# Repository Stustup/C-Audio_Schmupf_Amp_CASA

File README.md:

# Schmupf-Amp (CASA)
Small Stereo Headphone Amp with microphone passthrough fitting into a nice case.

Simple leader follower parallel opamp topology.

# Signal Path 
Input -> Filter -> Input switch -> Input Buffer -> Volume control -> Voltage Gain Stage -> Current Gain Stage -> Output

Bipolar linear post regulated power supply derived from 12V with a REC10K +-12V Module. Voltage for the opamps is +-9V.d

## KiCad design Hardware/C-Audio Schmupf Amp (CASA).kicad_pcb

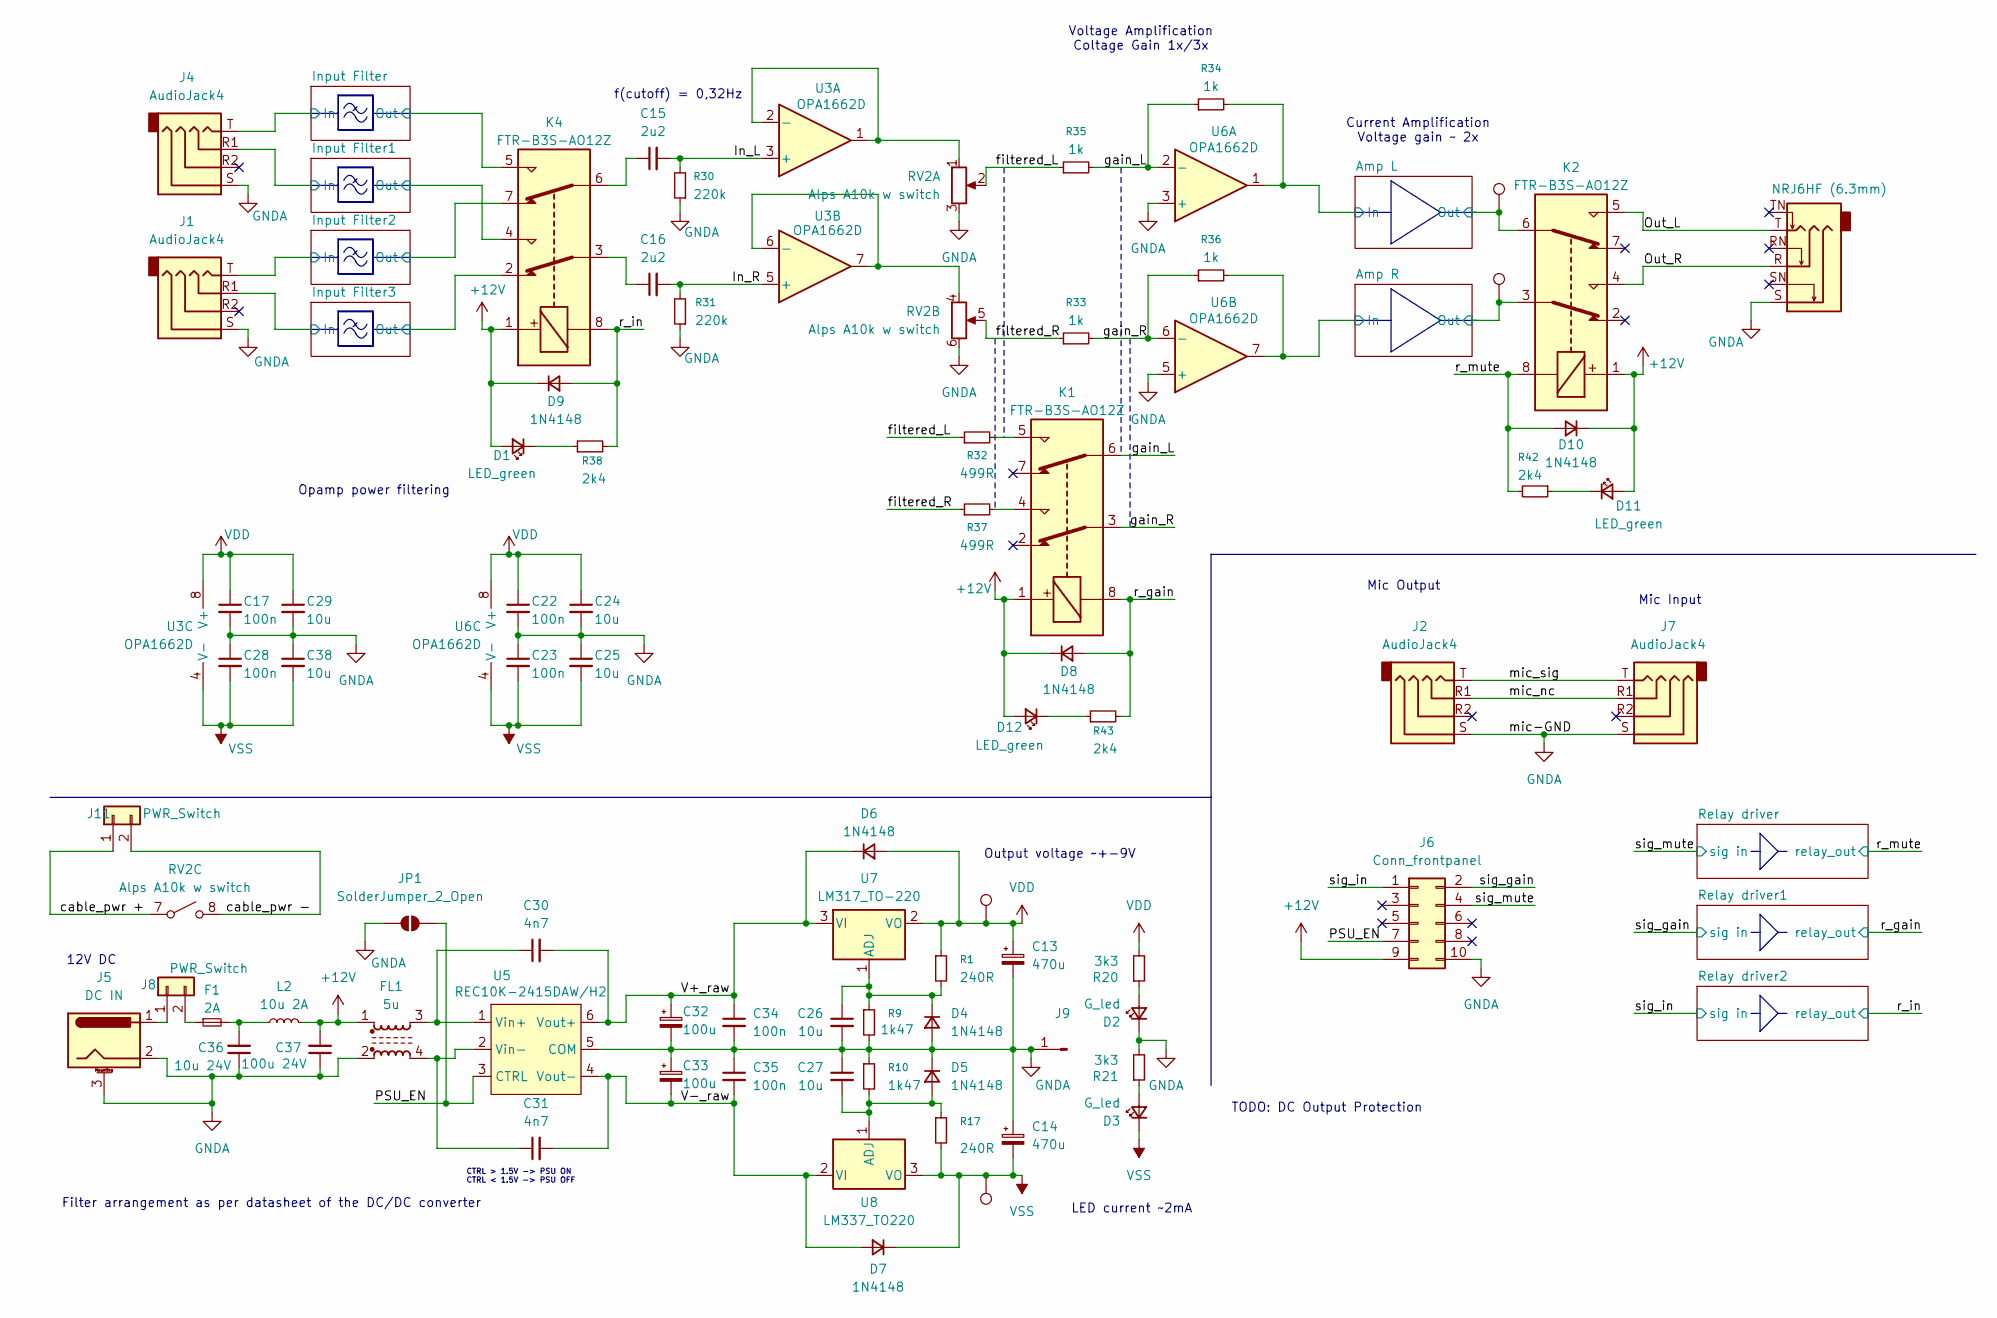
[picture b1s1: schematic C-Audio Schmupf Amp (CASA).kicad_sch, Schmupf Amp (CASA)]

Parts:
C13, C14: 470u; CP_Elec_10x10.5
C15, C16: 2u2; C_Rect_L10.3mm_W5.7mm_P7.50mm_MKS4
C17, C22, C23, C28, C34, C35: 100n; C_0805_2012Metric_Pad1.18x1.45mm_HandSolder
C24, C25, C26, C27, C29, C38: 10u; CP_Elec_4x5.8
C30, C31: 4n7; C_0805_2012Metric_Pad1.18x1.45mm_HandSolder
C32, C33: 100u; CP_Elec_6.3x7.7
C36: 10u 24V; CP_Elec_4x5.8
C37: 100u 24V; CP_Elec_4x5.8
D1, D11, D12: LED_green; LED_0805_2012Metric_Pad1.15x1.40mm_HandSolder
D2, D3: G_led; LED_0805_2012Metric
D4, D5, D6, D7, D8, D9, D10: 1N4148; D_0805_2012Metric_Pad1.15x1.40mm_HandSolder
F1: 2A; Fuseholder_Littelfuse_Nano2_154x
FL1: 5u; L_Bourns_SRF1260
J1, J2, J4, J7: AudioJack4; CLIFF_FC68125
J3: NRJ6HF (6.3mm); Jack_6.35mm_Neutrik_NMJ6HFD2_Horizontal
J5: DC IN; BarrelJack_CUI_PJ-102AH_Horizontal
J6: Conn_frontpanel; IDC-Header_2x05_P2.54mm_Vertical
J8, J11: PWR_Switch; TestPoint_2Pads_Pitch2.54mm_Drill0.8mm
J9: GND Conn; PinHeader_1x01_P1.00mm_Vertical
JP1: SolderJumper_2_Open; SolderJumper-2_P1.3mm_Open_TrianglePad1.0x1.5mm
K1, K2, K4: FTR-B3S-AO12Z; Relay_Fujitsu_FTR-B3S
L2: 10u 2A; L_APV_ANR4010
R1, R17: 240R; R_0805_2012Metric_Pad1.20x1.40mm_HandSolder
R9, R10: 1k47; R_0805_2012Metric_Pad1.20x1.40mm_HandSolder
R20, R21: 3k3; R_0805_2012Metric_Pad1.20x1.40mm_HandSolder
R30, R31: 220k; R_0805_2012Metric_Pad1.20x1.40mm_HandSolder
R32, R37: 499R; R_0805_2012Metric_Pad1.20x1.40mm_HandSolder
R33, R34, R35, R36: 1k; R_0805_2012Metric_Pad1.20x1.40mm_HandSolder
R38, R42, R43: 2k4; R_0805_2012Metric_Pad1.20x1.40mm_HandSolder
RV2: Alps A10k w switch; Potentiometer_Alps_RK097_Dual_Horizontal_Switch
TP1, TP4: TestPoint; TestPoint_Plated_Hole_D2.0mm
TP2: VDD; TestPoint_Pad_D1.0mm
TP3: VSS; TestPoint_Pad_D1.0mm
U3, U6: OPA1662D; SOIC-8_3.9x4.9mm_P1.27mm
U5: REC10K-2415DAW/H2; REC10K-2415DAWH2
U7: LM317_TO-220; TO-220-3_Vertical
U8: LM337_TO220; TO-220-3_Vertical

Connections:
+12V: C37.2, D1.2 (A), D8.1 (K), D9.1 (K), D10.1 (K), D11.2 (A), D12.2 (A), FL1.1, J6.9, K1.1, K2.1, K4.1, L2.2
/Amp L/In: R34.2, U6.1; also elsewhere on the board
/Amp L/Out: K2.6, TP1.1; also elsewhere on the board
/Amp R/In: R36.2, U6.7; also elsewhere on the board
/Amp R/Out: K2.3, TP4.1; also elsewhere on the board
/In_L: C15.2, R30.2, U3.3 (+)
/In_R: C16.2, R31.2, U3.5 (+)
/Input Filter1/In: J4.R1; also elsewhere on the board
/Input Filter1/Out: K4.4; also elsewhere on the board
/Input Filter2/In: J1.T; also elsewhere on the board
/Input Filter2/Out: K4.7; also elsewhere on the board
/Input Filter3/In: J1.R1; also elsewhere on the board
/Input Filter3/Out: K4.2; also elsewhere on the board
/Input Filter/In: J4.T; also elsewhere on the board
/Input Filter/Out: K4.5; also elsewhere on the board
/Out_L: J3.T, K2.5
/Out_R: J3.R, K2.4
/PSU_EN: J6.7, JP1.1 (A), U5.3 (CTRL)
/V+_raw: C30.2, C32.1, C34.1, D6.1 (K), U5.6 (Vout+), U7.3 (VI)
/V-_raw: C31.2, C33.2, C35.2, D7.2 (A), U5.4 (Vout-), U8.2 (VI)
/cable_pwr +: J11.1, RV2.7
/cable_pwr -: J11.2, RV2.8
/filtered_L: R32.1, R35.1, RV2.2
/filtered_R: R33.1, R37.1, RV2.5
/gain_L: K1.6, R34.1, R35.2, U6.2 (-)
/gain_R: K1.3, R33.2, R36.1, U6.6 (-)
/mic_nc: J2.R1, J7.R1
/mic_sig: J2.T, J7.T
/r_gain: D8.2 (A), K1.8, R43.2; also elsewhere on the board
/r_in: D9.2 (A), K4.8, R38.2; also elsewhere on the board
/r_mute: D10.2 (A), K2.8, R42.2; also elsewhere on the board
/sig_gain: J6.2; also elsewhere on the board
/sig_in: J6.1; also elsewhere on the board
/sig_mute: J6.4; also elsewhere on the board
GNDA: C13.2, C14.1, C17.2, C22.2, C23.1, C24.2, C25.1, C26.2, C27.1, C28.1, C29.2, C32.2, C33.1, C34.2, C35.1, C36.1, C37.1, C38.1, D2.1 (K), D4.2 (A), D5.1 (K), FL1.2, J1.S, J2.S, J3.S, J4.S, J5.2, J5.3 (MountPin), J6.10, J7.S, J9.1, JP1.2 (B), R9.2, R10.1, R21.2, R30.1, R31.1, RV2.3, RV2.6, U5.5 (COM), U6.3 (+), U6.5 (+); also elsewhere on the board
unnamed: C15.1, K4.6
unnamed: C16.1, K4.3
unnamed: C36.2, F1.2, L2.1
unnamed: D1.1 (K), R38.1
unnamed: D2.2 (A), R20.1
unnamed: D3.2 (A), R21.1
unnamed: C26.1, D4.1 (K), R1.2, R9.1, U7.1 (ADJ)
unnamed: C27.2, D5.2 (A), R10.2, R17.1, U8.1 (ADJ)
unnamed: D11.1 (K), R42.1
unnamed: D12.1 (K), R43.1
unnamed: J5.1, J8.1
unnamed: F1.1, J8.2
unnamed: K1.4, R37.2
unnamed: K1.5, R32.2
unnamed: RV2.1, U3.1, U3.2 (-)
unnamed: RV2.4, U3.6 (-), U3.7
unnamed: C30.1, FL1.3, U5.1 (Vin+)
unnamed: C31.1, FL1.4, U5.2 (Vin-)
VDD: C13.1, C17.1, C22.1, C24.1, C29.1, D6.2 (A), R1.1, R20.2, TP2.1, U3.8 (V+), U6.8 (V+), U7.2 (VO); also elsewhere on the board
VSS: C14.2, C23.2, C25.2, C28.2, C38.2, D3.1 (K), D7.1 (K), R17.2, TP3.1, U3.4 (V-), U6.4 (V-), U8.3 (VO); also elsewhere on the board

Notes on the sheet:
Output voltage ~+-9V
f(cutoff) = 0,32Hz
Mic Input
Mic Output
Filter arrangement as per datasheet of the DC/DC converter
12V DC
Voltage Amplification Coltage Gain 1x/3x
CTRL > 1.5V -> PSU ON CTRL < 1.5V -> PSU OFF
LED current ~2mA
TODO: DC Output Protection
Current Amplification Voltage gain ~ 2x
Opamp power filtering

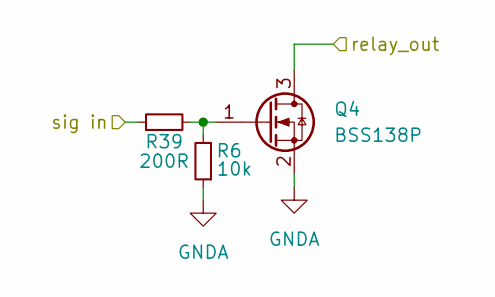
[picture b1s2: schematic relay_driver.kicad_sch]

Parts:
Q4: BSS138P; SOT-23
R6: 10k; R_0805_2012Metric_Pad1.20x1.40mm_HandSolder
R39: 200R; R_0805_2012Metric_Pad1.20x1.40mm_HandSolder

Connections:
/r_mute: Q4.3 (D); also elsewhere on the board
/sig_mute: R39.1; also elsewhere on the board
GNDA: Q4.2 (S), R6.1; also elsewhere on the board
unnamed: Q4.1 (G), R6.2, R39.2

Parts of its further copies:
Q5, Q6: BSS138P; SOT-23
R18, R19: 10k; R_0805_2012Metric_Pad1.20x1.40mm_HandSolder
R40, R41: 200R; R_0805_2012Metric_Pad1.20x1.40mm_HandSolder

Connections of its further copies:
/r_gain: Q5.3 (D); also elsewhere on the board
/r_in: Q6.3 (D); also elsewhere on the board
/sig_gain: R40.1; also elsewhere on the board
/sig_in: R41.1; also elsewhere on the board
GNDA: Q5.2 (S), Q6.2 (S), R18.1, R19.1; also elsewhere on the board
unnamed: Q5.1 (G), R18.2, R40.2
unnamed: Q6.1 (G), R19.2, R41.2

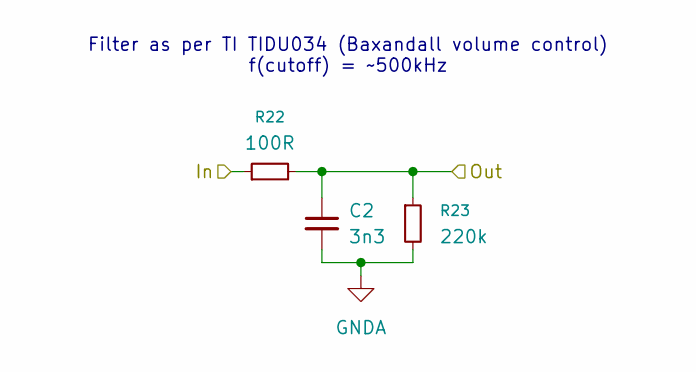
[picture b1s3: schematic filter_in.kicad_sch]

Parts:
C2: 3n3; C_0805_2012Metric_Pad1.18x1.45mm_HandSolder
R22: 100R; R_0805_2012Metric_Pad1.20x1.40mm_HandSolder
R23: 220k; R_0805_2012Metric_Pad1.20x1.40mm_HandSolder

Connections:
/Input Filter/In: R22.1; also elsewhere on the board
/Input Filter/Out: C2.1, R22.2, R23.1; also elsewhere on the board
GNDA: C2.2, R23.2; also elsewhere on the board

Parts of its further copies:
C3, C8, C9: 3n3; C_0805_2012Metric_Pad1.18x1.45mm_HandSolder
R24, R26, R28: 100R; R_0805_2012Metric_Pad1.20x1.40mm_HandSolder
R25, R27, R29: 220k; R_0805_2012Metric_Pad1.20x1.40mm_HandSolder

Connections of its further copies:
/Input Filter1/In: R24.1; also elsewhere on the board
/Input Filter1/Out: C3.1, R24.2, R25.1; also elsewhere on the board
/Input Filter2/In: R26.1; also elsewhere on the board
/Input Filter2/Out: C8.1, R26.2, R27.1; also elsewhere on the board
/Input Filter3/In: R28.1; also elsewhere on the board
/Input Filter3/Out: C9.1, R28.2, R29.1; also elsewhere on the board
GNDA: C3.2, C8.2, C9.2, R25.2, R27.2, R29.2; also elsewhere on the board

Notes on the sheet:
Filter as per TI TIDU034 (Baxandall volume control) f(cutoff) = ~500kHz

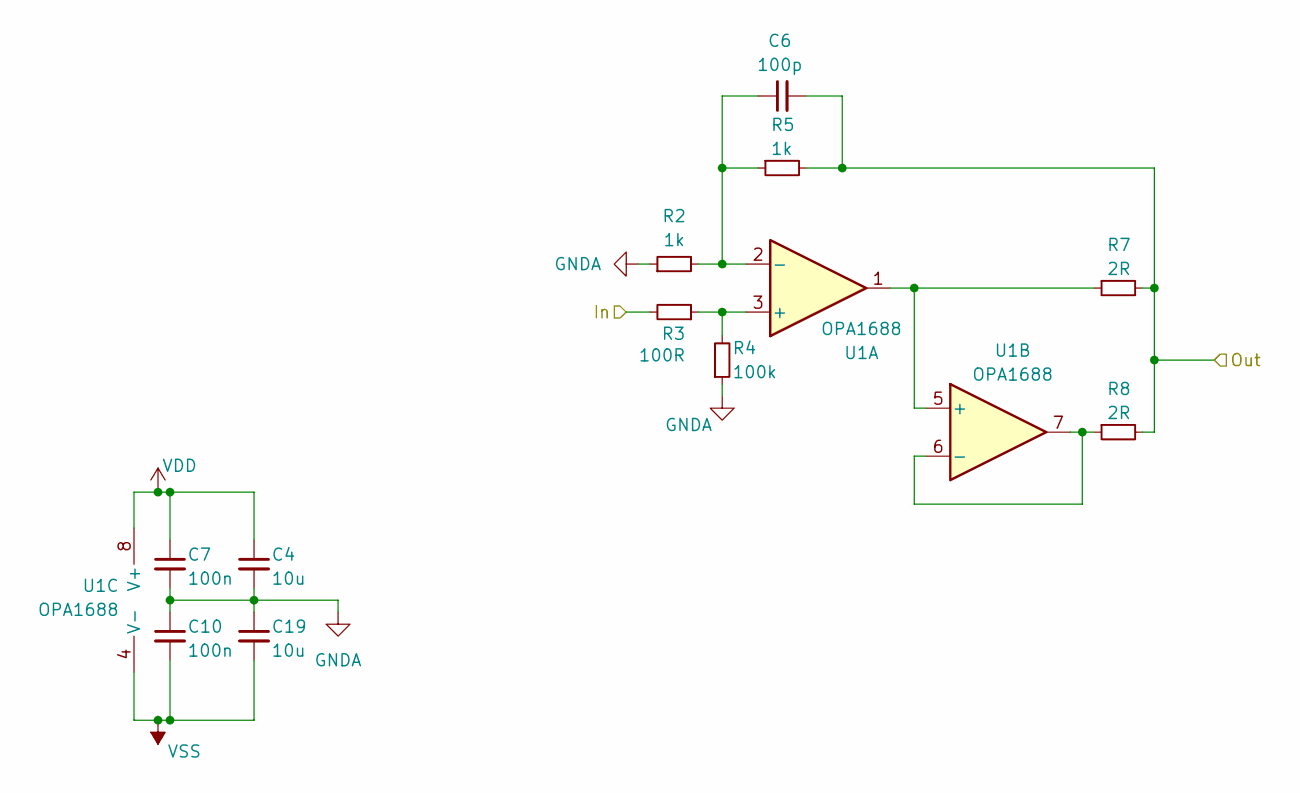
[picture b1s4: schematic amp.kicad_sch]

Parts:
C4, C19: 10u; CP_Elec_4x5.8
C6: 100p; C_0805_2012Metric_Pad1.18x1.45mm_HandSolder
C7, C10: 100n; C_0805_2012Metric_Pad1.18x1.45mm_HandSolder
R2, R5: 1k; R_0805_2012Metric_Pad1.20x1.40mm_HandSolder
R3: 100R; R_0805_2012Metric_Pad1.20x1.40mm_HandSolder
R4: 100k; R_0805_2012Metric_Pad1.20x1.40mm_HandSolder
R7, R8: 2R; R_0805_2012Metric_Pad1.20x1.40mm_HandSolder
U1: OPA1688; SO-8_3.9x4.9mm_P1.27mm

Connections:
/Amp L/In: R3.2; also elsewhere on the board
/Amp L/Out: C6.2, R5.2, R7.2, R8.2; also elsewhere on the board
GNDA: C4.2, C7.2, C10.1, C19.1, R2.1, R4.1; also elsewhere on the board
unnamed: R3.1, R4.2, U1.3 (+)
unnamed: C6.1, R2.2, R5.1, U1.2 (-)
unnamed: R7.1, U1.1, U1.5 (+)
unnamed: R8.1, U1.6 (-), U1.7
VDD: C4.1, C7.1, U1.8 (V+); also elsewhere on the board
VSS: C10.2, C19.2, U1.4 (V-); also elsewhere on the board

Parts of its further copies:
C5, C20: 10u; CP_Elec_4x5.8
C11, C18: 100n; C_0805_2012Metric_Pad1.18x1.45mm_HandSolder
C21: 100p; C_0805_2012Metric_Pad1.18x1.45mm_HandSolder
R11, R14: 1k; R_0805_2012Metric_Pad1.20x1.40mm_HandSolder
R12: 100R; R_0805_2012Metric_Pad1.20x1.40mm_HandSolder
R13: 100k; R_0805_2012Metric_Pad1.20x1.40mm_HandSolder
R15, R16: 2R; R_0805_2012Metric_Pad1.20x1.40mm_HandSolder
U2: OPA1688; SO-8_3.9x4.9mm_P1.27mm

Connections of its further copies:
/Amp R/In: R12.2; also elsewhere on the board
/Amp R/Out: C21.2, R14.2, R15.2, R16.2; also elsewhere on the board
GNDA: C5.2, C11.2, C18.1, C20.1, R11.1, R13.1; also elsewhere on the board
unnamed: R12.1, R13.2, U2.3 (+)
unnamed: C21.1, R11.2, R14.1, U2.2 (-)
unnamed: R15.1, U2.1, U2.5 (+)
unnamed: R16.1, U2.6 (-), U2.7
VDD: C5.1, C11.1, U2.8 (V+); also elsewhere on the board
VSS: C18.2, C20.2, U2.4 (V-); also elsewhere on the board

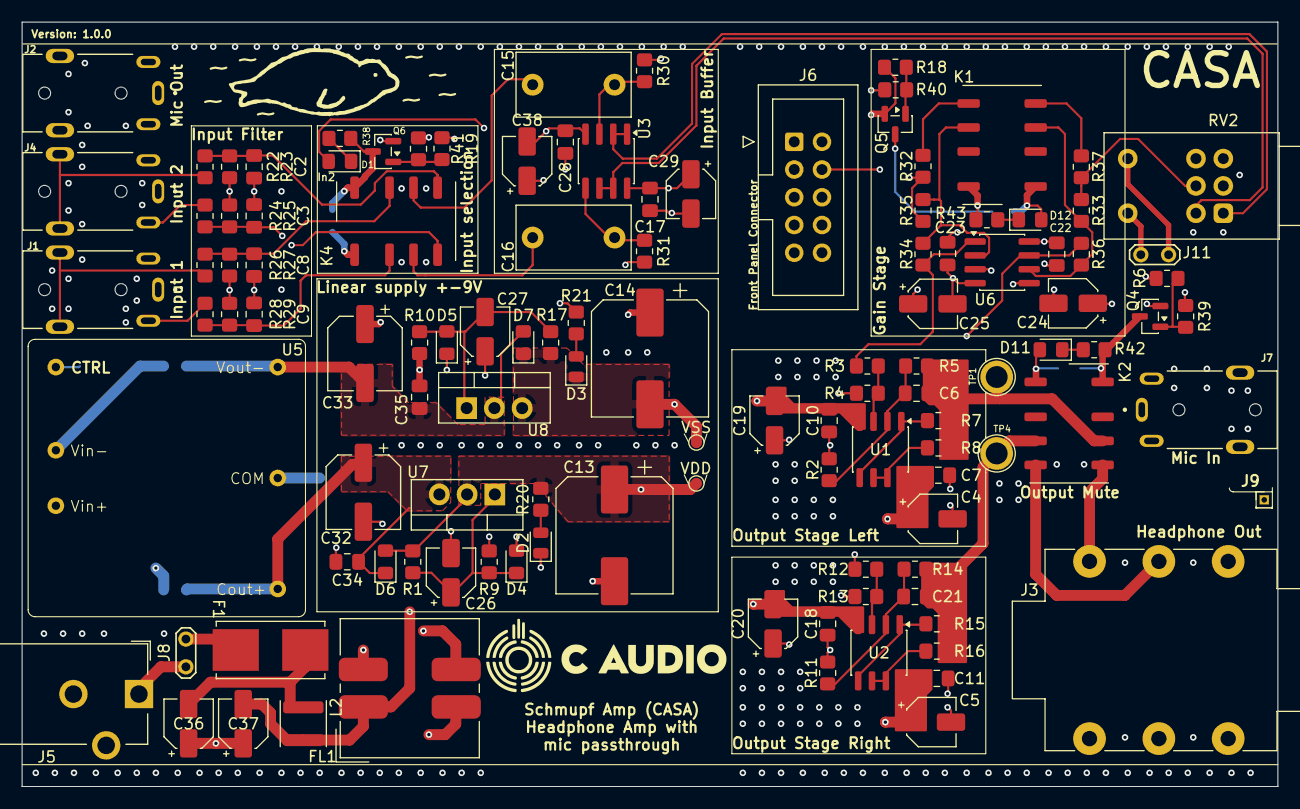
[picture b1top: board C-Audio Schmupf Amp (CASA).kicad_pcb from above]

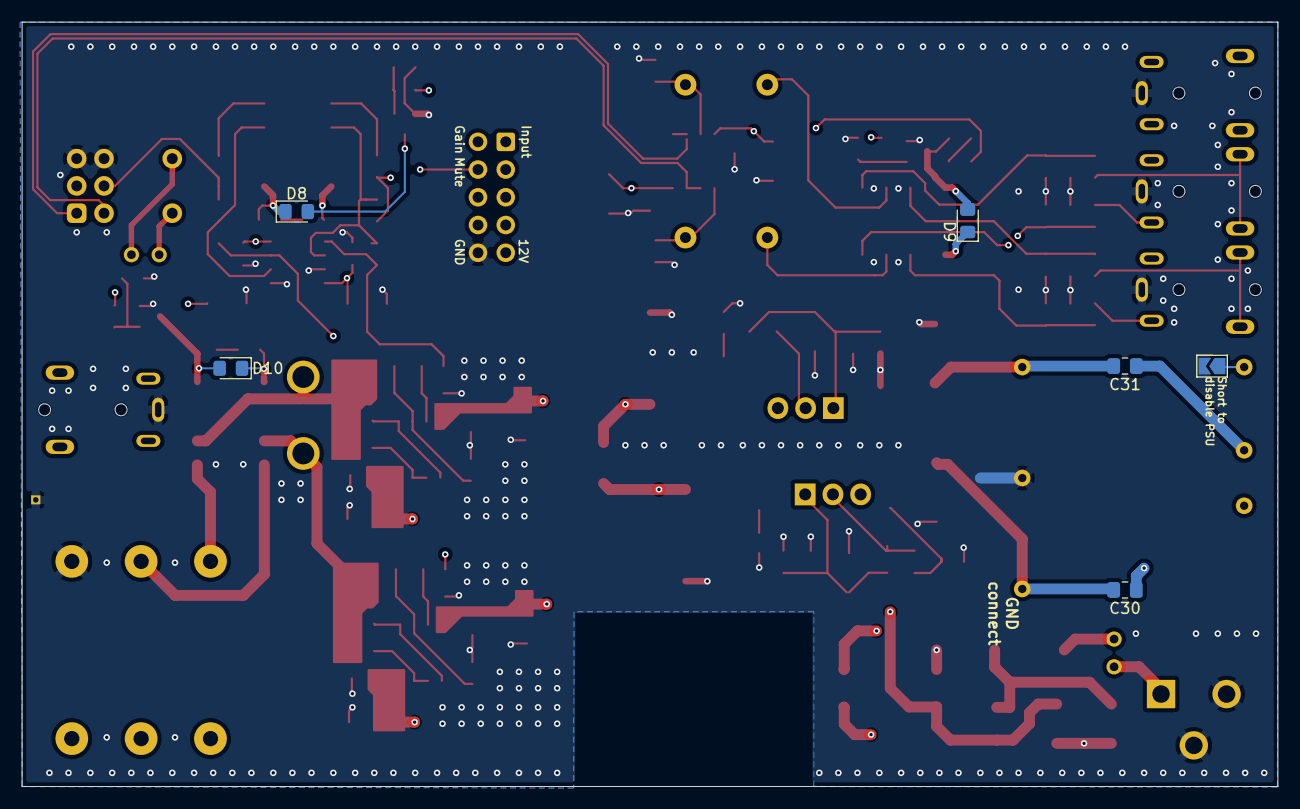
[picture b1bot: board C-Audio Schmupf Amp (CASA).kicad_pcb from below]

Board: 4 copper layers, 115.0 x 70.0 mm, 123 parts (6 on the bottom side), 66 nets.

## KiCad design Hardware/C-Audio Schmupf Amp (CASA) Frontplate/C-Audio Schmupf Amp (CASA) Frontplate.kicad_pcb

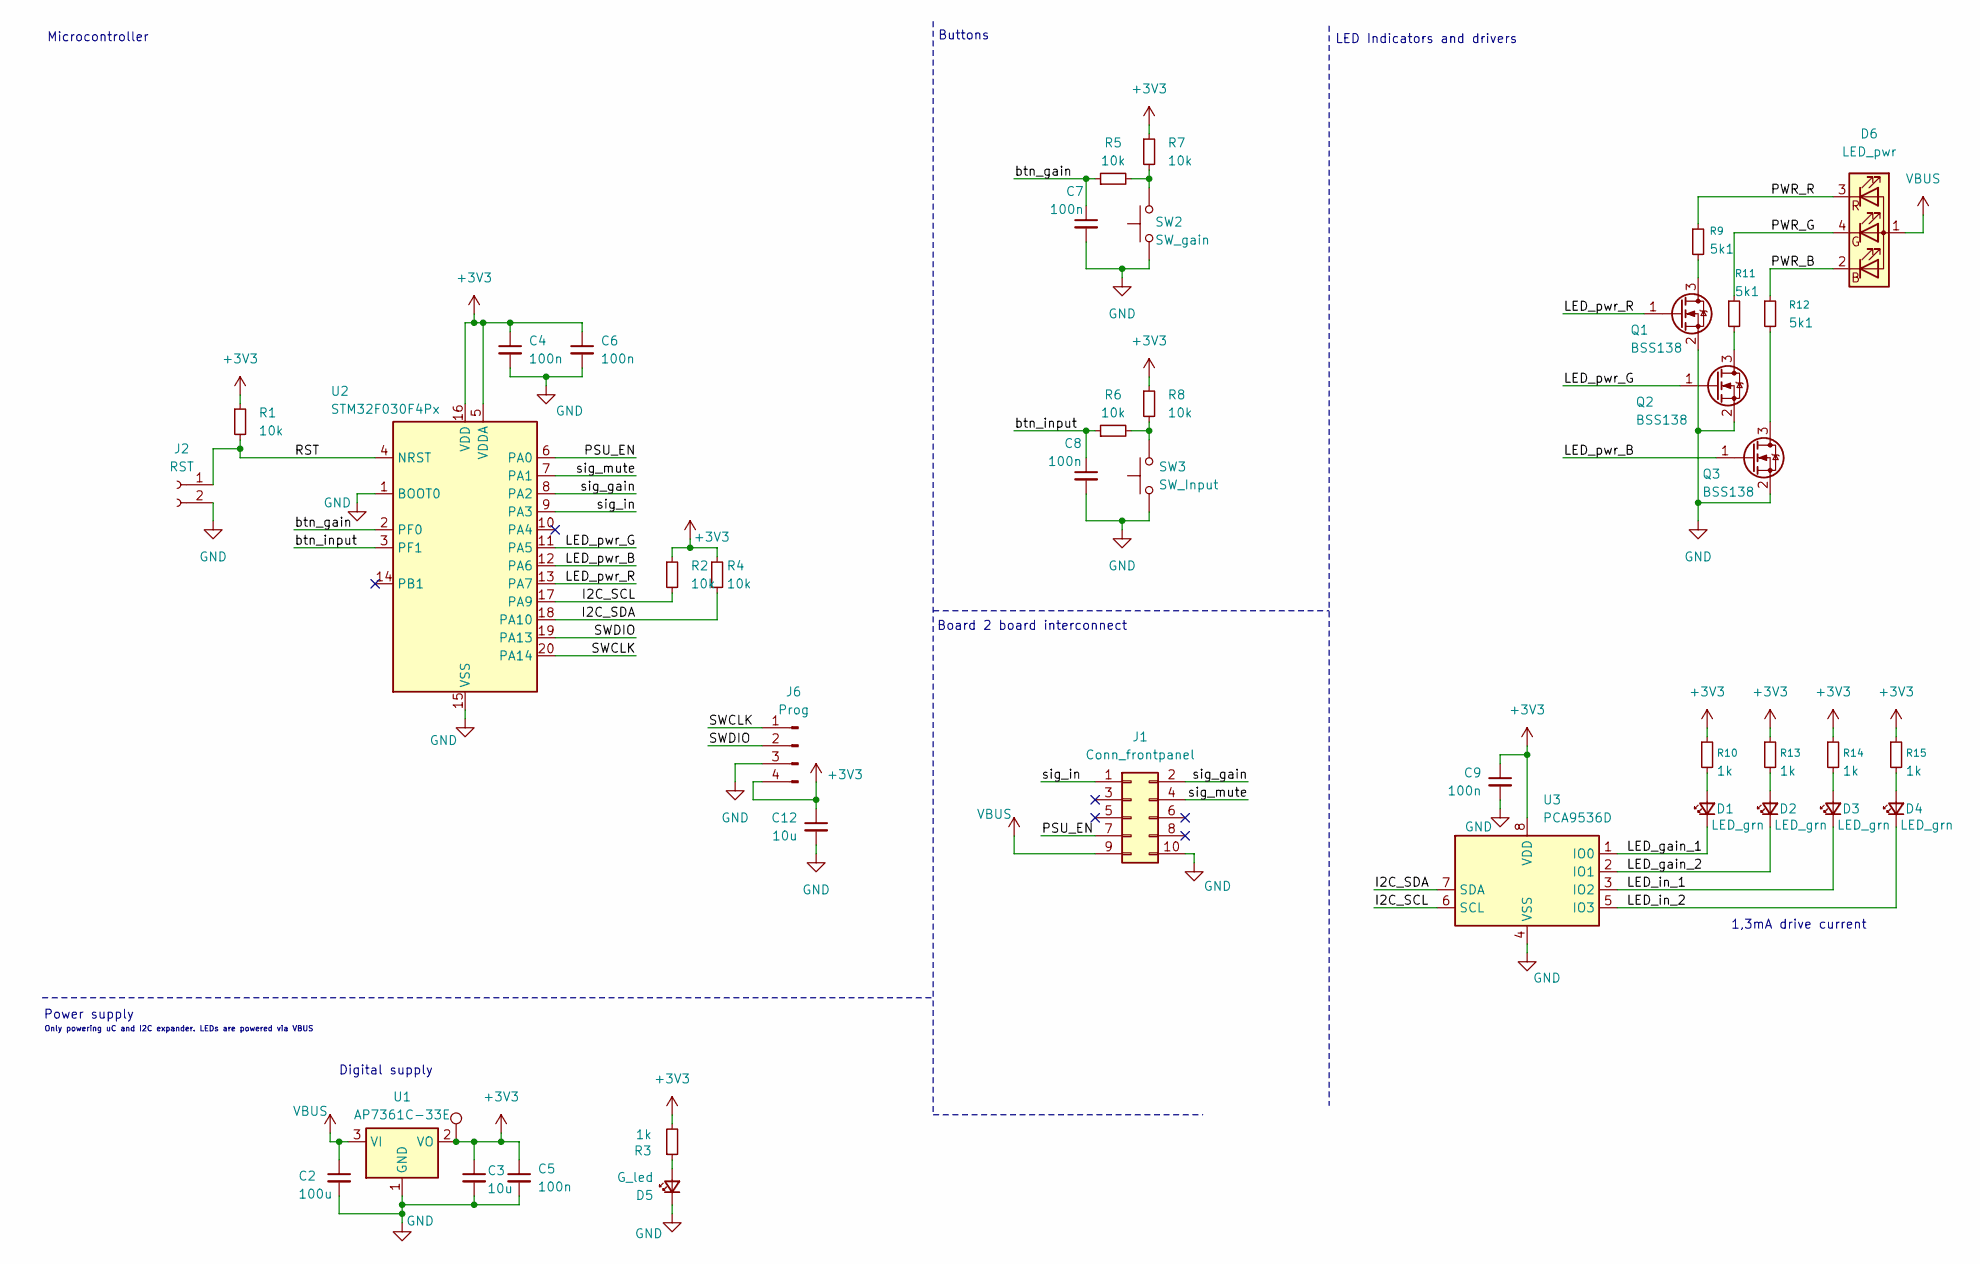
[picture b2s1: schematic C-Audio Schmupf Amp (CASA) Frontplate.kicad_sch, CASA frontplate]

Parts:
C2: 100u; CP_Elec_4x5.8
C3: 10u; C_0805_2012Metric_Pad1.18x1.45mm_HandSolder
C4, C5, C6, C7, C8, C9: 100n; C_0805_2012Metric_Pad1.18x1.45mm_HandSolder
C12: 10u; C_0805_2012Metric_Pad1.18x1.45mm_HandSolder; Mouser Nr. 187-CL21B106KPQNNNE
D1, D2, D3, D4: LED_grn; LED_0805_2012Metric_Pad1.15x1.40mm_HandSolder
D5: G_led; LED_0805_2012Metric_Pad1.15x1.40mm_HandSolder
D6: LED_pwr; LED_RGB_Wuerth-PLCC4_3.2x2.8mm_150141M173100
J1: Conn_frontpanel; IDC-Header_2x05_P2.54mm_Vertical
J2: RST; SolderJumper-2_P1.3mm_Open_TrianglePad1.0x1.5mm
J6: Prog; PinHeader_1x04_P2.54mm_Vertical
Q1, Q2, Q3: BSS138; SOT-23
R1, R2, R4, R5, R6, R7, R8: 10k; R_0805_2012Metric_Pad1.20x1.40mm_HandSolder
R3, R10, R13, R14, R15: 1k; R_0805_2012Metric_Pad1.20x1.40mm_HandSolder
R9, R11, R12: 5k1; R_0805_2012Metric_Pad1.20x1.40mm_HandSolder
SW2: SW_gain; SW_PUSH_6mm_H13mm
SW3: SW_Input; SW_PUSH_6mm_H13mm
TP1: TestPoint; TestPoint_Pad_D1.0mm
U1: AP7361C-33E; SOT-223-3_TabPin2; Mouser Nr. 621-AP7361C-33ER-13
U2: STM32F030F4Px; TSSOP-20_4.4x6.5mm_P0.65mm
U3: PCA9536D; SOIC-8_3.9x4.9mm_P1.27mm

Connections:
/I2C_SCL: R2.2, U2.17 (PA9), U3.6 (SCL)
/I2C_SDA: R4.2, U2.18 (PA10), U3.7 (SDA)
/LED_gain_1: D1.1 (K), U3.1 (IO0)
/LED_gain_2: D2.1 (K), U3.2 (IO1)
/LED_in_1: D3.1 (K), U3.3 (IO2)
/LED_in_2: D4.1 (K), U3.5 (IO3)
/LED_pwr_B: Q3.1 (G), U2.12 (PA6)
/LED_pwr_G: Q2.1 (G), U2.11 (PA5)
/LED_pwr_R: Q1.1 (G), U2.13 (PA7)
/PSU_EN: J1.7, U2.6 (PA0)
/PWR_B: D6.2 (BK), R12.1
/PWR_G: D6.4 (GK), R11.1
/PWR_R: D6.3 (RK), R9.1
/RST: J2.1, R1.2, U2.4 (NRST)
/SWCLK: J6.1, U2.20 (PA14)
/SWDIO: J6.2, U2.19 (PA13)
/btn_gain: C7.1, R5.1, U2.2 (PF0)
/btn_input: C8.1, R6.1, U2.3 (PF1)
/sig_gain: J1.2, U2.8 (PA2)
/sig_in: J1.1, U2.9 (PA3)
/sig_mute: J1.4, U2.7 (PA1)
GND: C2.2, C3.2, C4.2, C5.2, C6.2, C7.2, C8.2, C9.2, C12.2, D5.1 (K), J1.10, J2.2, J6.3, Q1.2 (S), Q2.2 (S), Q3.2 (S), SW2.1, SW3.1, U1.1 (GND), U2.1 (BOOT0), U2.15 (VSS), U3.4 (VSS)
unnamed: D1.2 (A), R10.2
unnamed: D2.2 (A), R13.2
unnamed: D3.2 (A), R14.2
unnamed: D4.2 (A), R15.2
unnamed: D5.2 (A), R3.1
unnamed: Q1.3 (D), R9.2
unnamed: Q2.3 (D), R11.2
unnamed: Q3.3 (D), R12.2
unnamed: R5.2, R7.2, SW2.2
unnamed: R6.2, R8.2, SW3.2

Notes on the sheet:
Board 2 board interconnect
Microcontroller
Digital supply
Buttons
1,3mA drive current
Only powering uC and I2C expander. LEDs are powered via VBUS
Power supply
LED Indicators and drivers

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
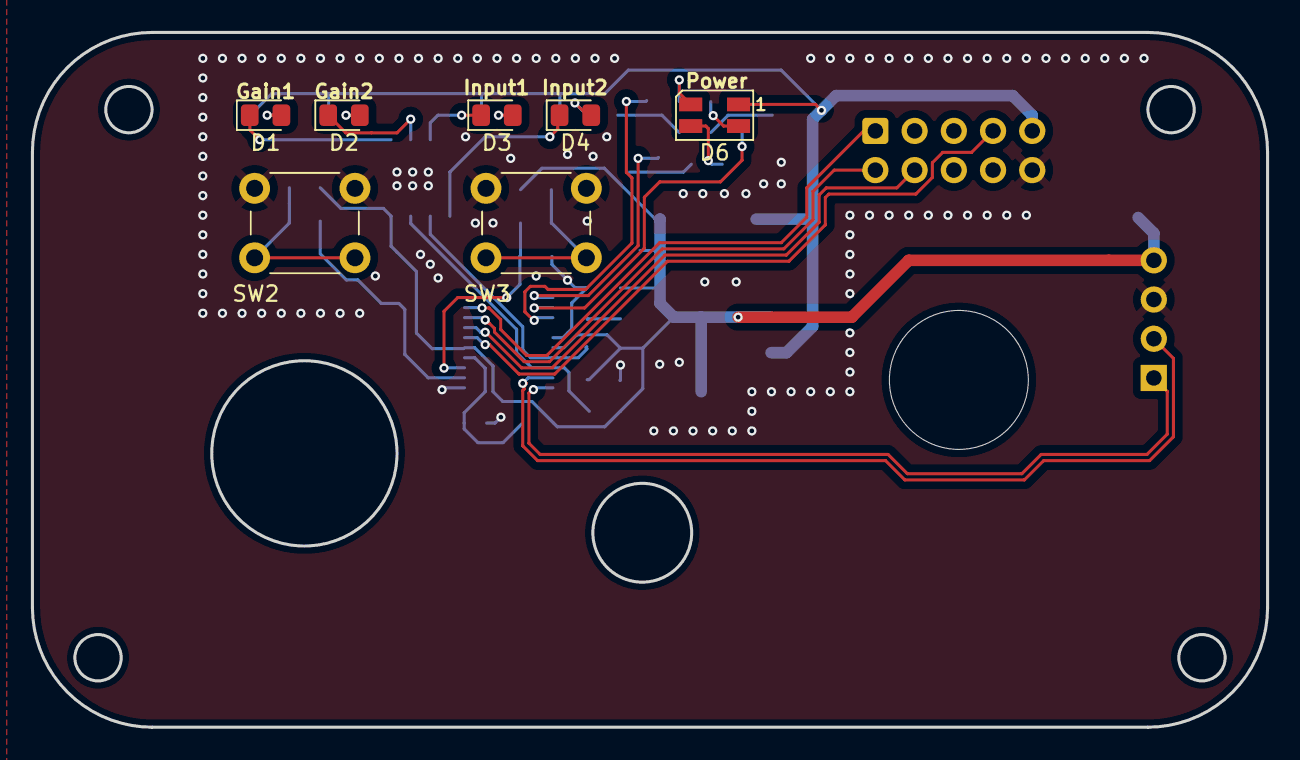
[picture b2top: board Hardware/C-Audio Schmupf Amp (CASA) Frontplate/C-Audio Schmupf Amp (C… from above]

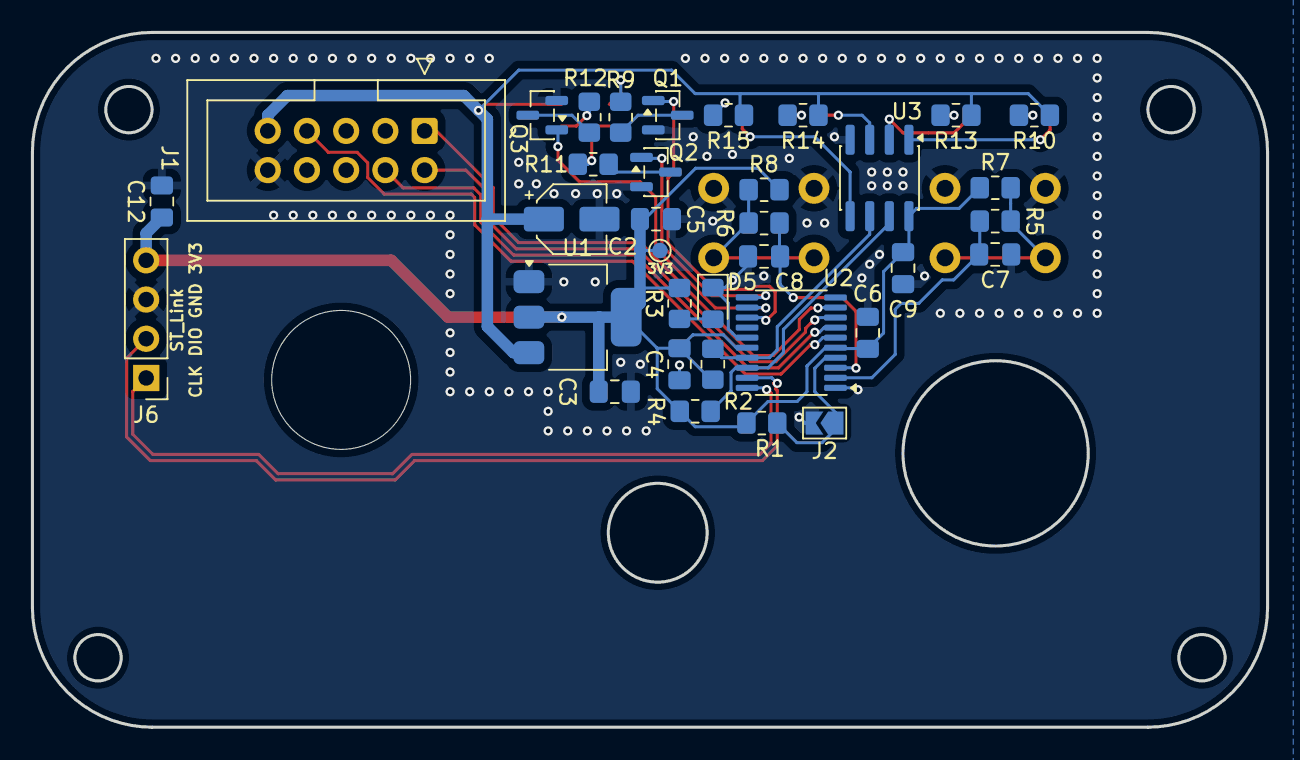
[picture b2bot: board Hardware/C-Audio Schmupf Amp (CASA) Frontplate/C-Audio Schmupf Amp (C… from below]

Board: 2 copper layers, 80.0 x 45.0 mm, 42 parts (35 on the bottom side), 34 nets.

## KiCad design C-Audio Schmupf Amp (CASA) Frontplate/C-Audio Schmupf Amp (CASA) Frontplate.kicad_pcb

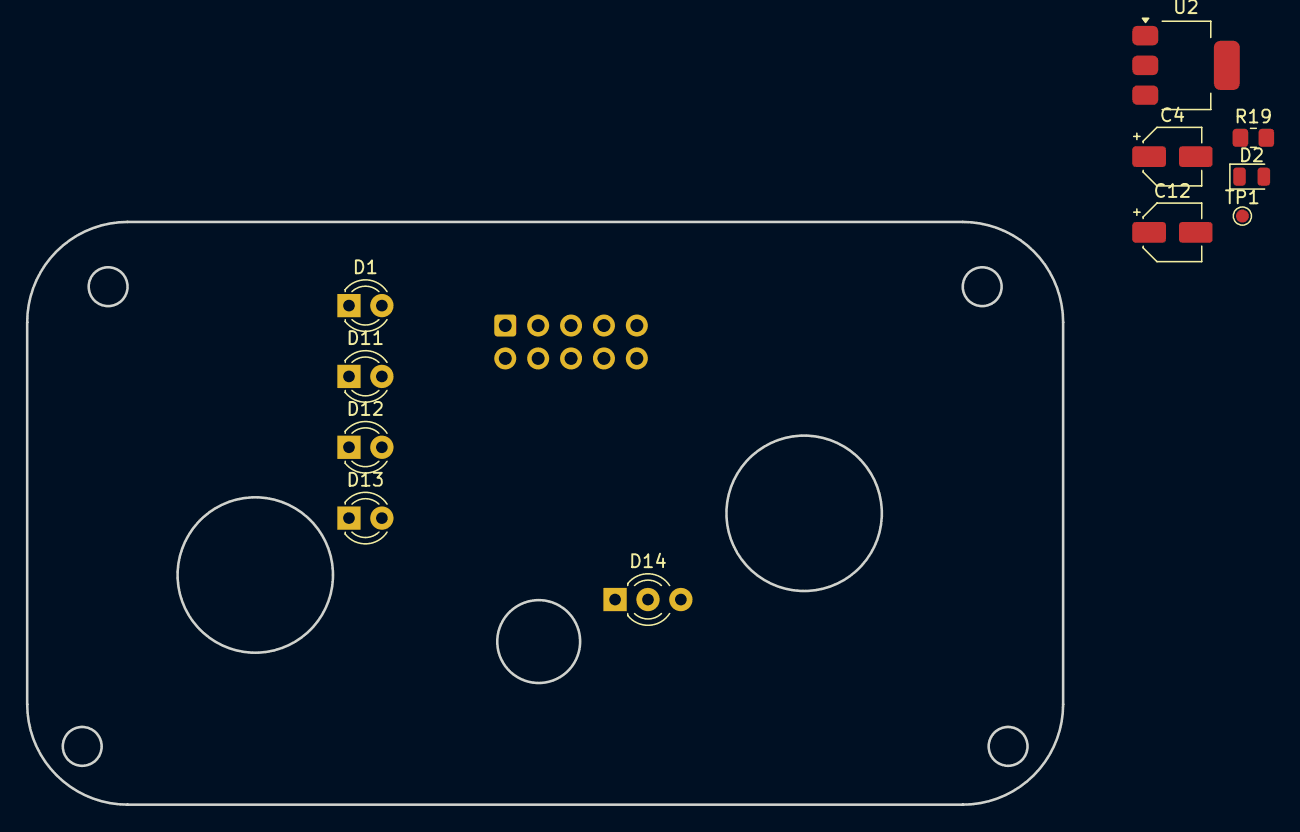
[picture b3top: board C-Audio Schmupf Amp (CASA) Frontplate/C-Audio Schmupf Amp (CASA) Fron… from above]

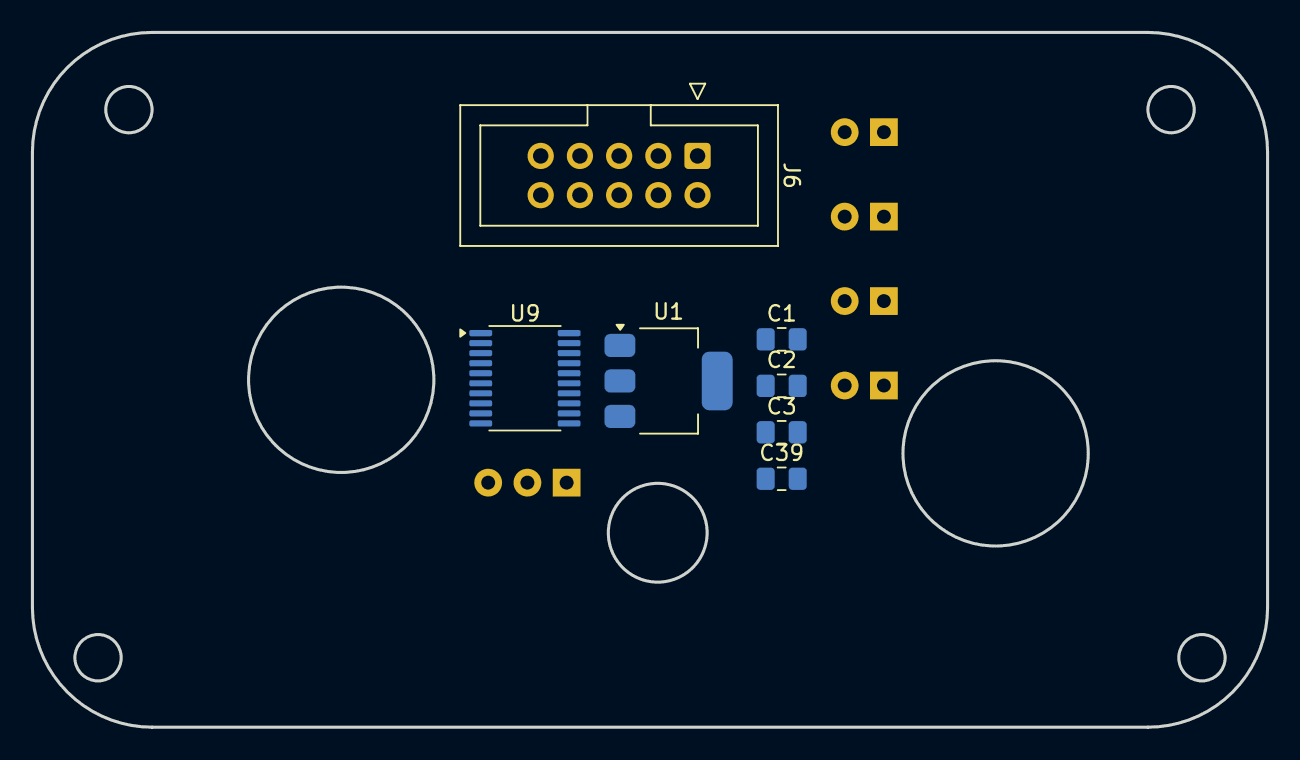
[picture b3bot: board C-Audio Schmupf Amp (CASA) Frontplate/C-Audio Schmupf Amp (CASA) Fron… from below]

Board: 2 copper layers, 80.0 x 45.0 mm, 18 parts (7 on the bottom side), 5 nets, no tracks yet.

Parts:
C1, C39: 100n; C_0805_2012Metric_Pad1.18x1.45mm_HandSolder
C2: 1u; C_0805_2012Metric_Pad1.18x1.45mm_HandSolder
C3: 4u7; C_0805_2012Metric_Pad1.18x1.45mm_HandSolder
C4, C12: 10u; CP_Elec_4x5.8
D1, D11, D12, D13: LED_w; LED_D3.0mm_Clear
D2: G_led; LED_0805_2012Metric
D14: LED_PWR; LED_D3.0mm-3
J6: Conn_frontpanel; IDC-Header_2x05_P2.54mm_Vertical
R19: 1k; R_0805_2012Metric_Pad1.20x1.40mm_HandSolder
TP1: TestPoint; TestPoint_Pad_D1.0mm
U1, U2: AP7361C-33E; SOT-223-3_TabPin2
U9: STM32F030F4Px; TSSOP-20_4.4x6.5mm_P0.65mm

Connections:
+3V3: C3.1, C4.1, R19.2, TP1.1, U1.3 (VO), U2.3 (VO)
+5V: C2.1, U1.1 (VI)
GND: C2.2, C3.2, C4.2, C12.2, D2.1 (K), D14.3 (K), U1.2 (GND), U2.2 (GND)
unnamed: D2.2 (A), R19.1
VBUS: C12.1, U2.1 (VI)
